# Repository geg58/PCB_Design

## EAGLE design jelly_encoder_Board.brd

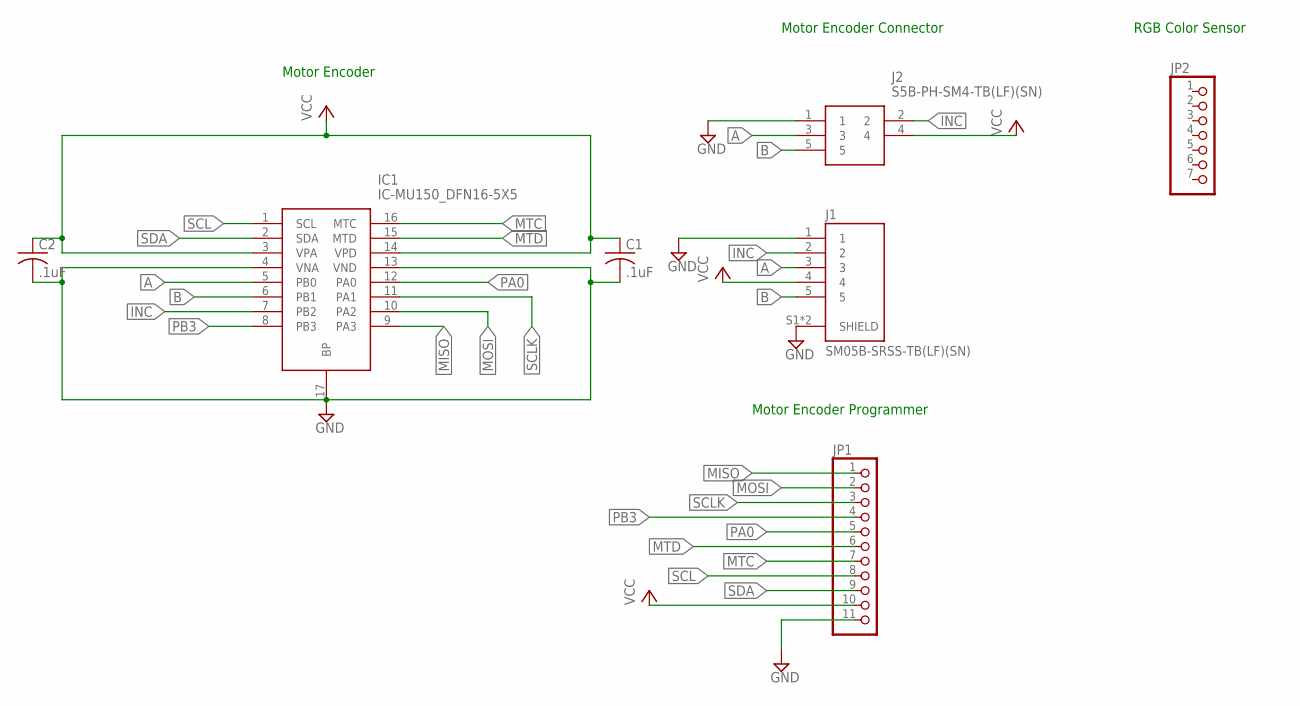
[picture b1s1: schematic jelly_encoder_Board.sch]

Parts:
C1, C2: .1uF; C0603
IC1: IC-MU150_DFN16-5X5; SON50P500X500X100-17N
J1: SM05B-SRSS-TB(LF)(SN); JST_SM05B-SRSS-TB(LF)(SN)
J2: S5B-PH-SM4-TB(LF)(SN); S5B-PH-SM4-TB_1
JP1: PINHD-1X11/90; 1X11/90
JP2: PINHD-1X7/90; 1X07/90

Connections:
A: IC1.5 (PB0), J1.3, J2.3
B: IC1.6 (PB1), J1.5, J2.5
GND: C1.2, C2.2, IC1.4 (VNA), IC1.13 (VND), IC1.17 (BP), J1.1, J1.S1 (SHIELD), J1.S2 (SHIELD), J2.1, JP1.11
INC: IC1.7 (PB2), J1.2, J2.2
MISO: IC1.9 (PA3), JP1.1
MOSI: IC1.10 (PA2), JP1.2
MTC: IC1.16 (MTC), JP1.7
MTD: IC1.15 (MTD), JP1.6
PA0: IC1.12 (PA0), JP1.5
PB3: IC1.8 (PB3), JP1.4
SCL: IC1.1 (SCL), JP1.8
SCLK: IC1.11 (PA1), JP1.3
SDA: IC1.2 (SDA), JP1.9
VCC: C1.1, C2.1, IC1.3 (VPA), IC1.14 (VPD), J1.4, J2.4, JP1.10

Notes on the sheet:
Motor Encoder Connector
Motor Encoder
Motor Encoder Programmer
RGB Color Sensor

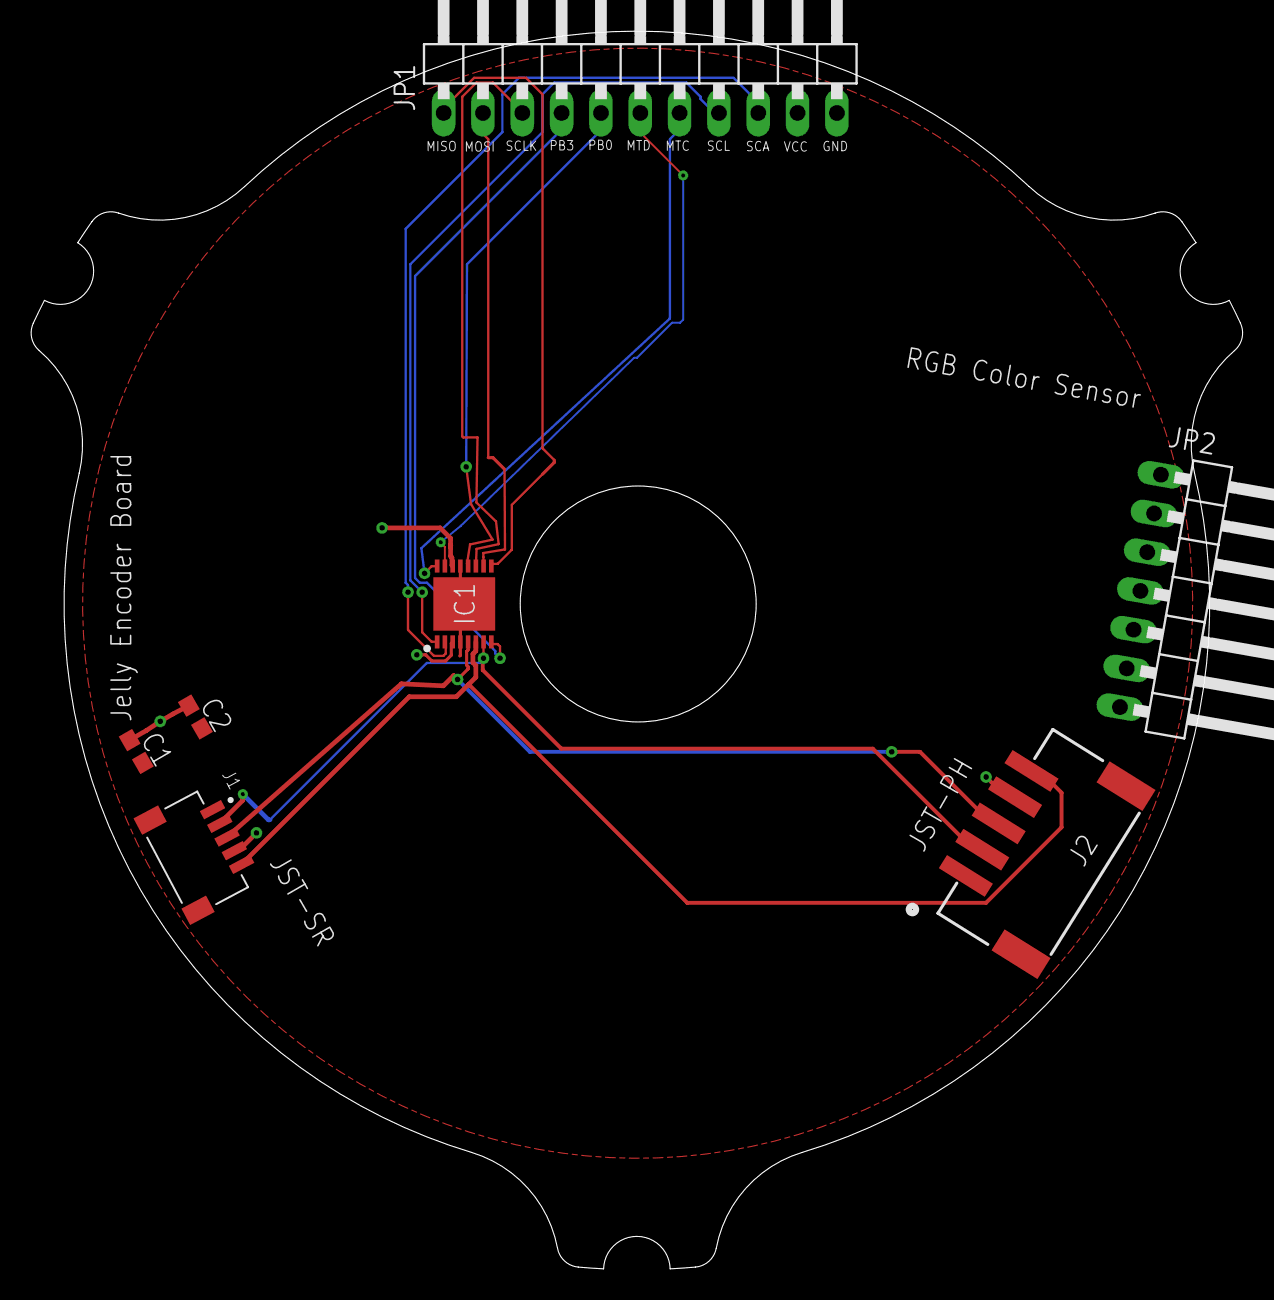
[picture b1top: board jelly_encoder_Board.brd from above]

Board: 2 copper layers, 78.3 x 79.9 mm, 7 parts (0 on the bottom side), 14 nets.

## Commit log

2019-11-10 initial board design
2019-11-10 added image
2019-11-10 added debug pins
2019-11-10 added second connector for JST-PH and fixed routes
2019-11-10 fixed image
2019-11-10 added RGB Sensor pins
2019-11-11 fixed traces and added decoupling caps
2019-11-11 fixed layout and other things
